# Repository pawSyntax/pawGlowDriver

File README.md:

# pawGlowDriver
Glow plug driver for multicyliner model ic engines. 
Can be used with 1-9 cylinders. Powered by 3 cell lipo. Interfaces with rc receiver for engine starting and variable onboard glow plug control. 
Arduino code to run on pro-mini. Eagle schematic and board files. CamBam file for pcb cutting.

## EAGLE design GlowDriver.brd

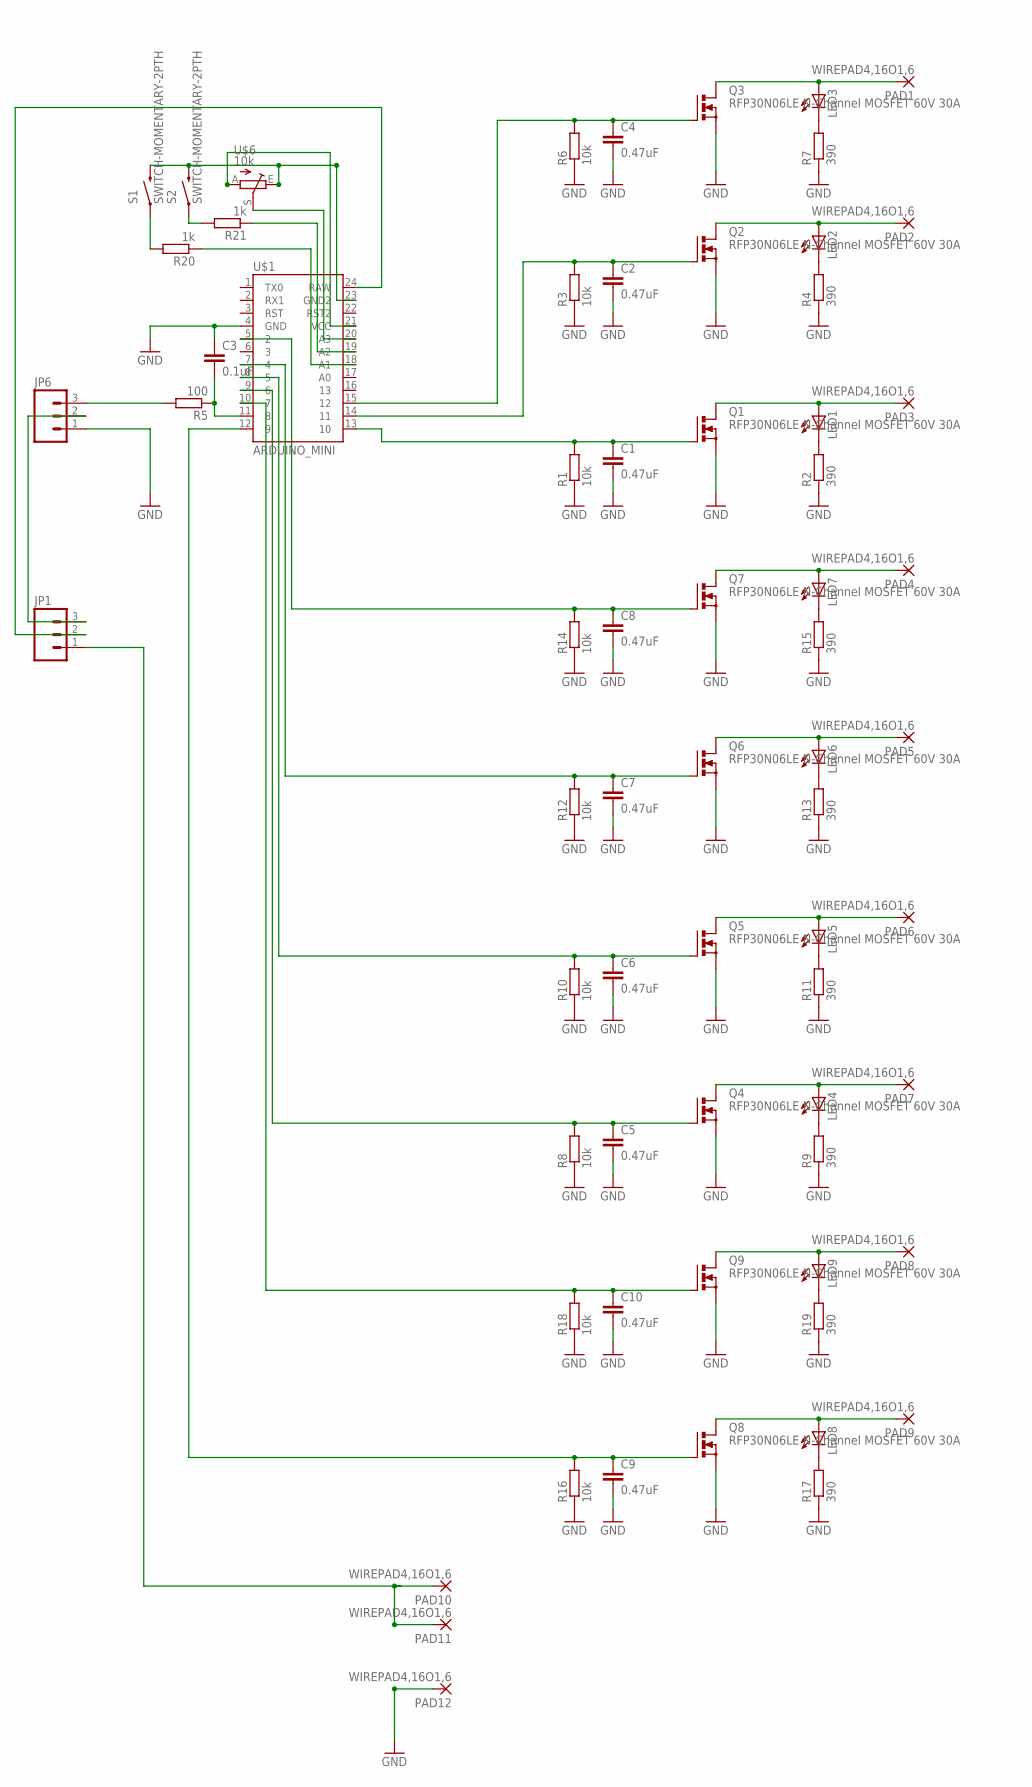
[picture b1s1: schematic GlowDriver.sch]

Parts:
C1, C2, C4, C5, C6, C7, C8, C9, C10: 0.47uF; CAP-PTH-SMALLEZ
C3: 0.1uF; C050-035X075
JP1, JP6: M03PTH; 1X03
LED1, LED2, LED3, LED4, LED5, LED6, LED7, LED8, LED9: LED5MM
PAD1, PAD2, PAD3, PAD4, PAD5, PAD6, PAD7, PAD8, PAD9, PAD10, PAD11, PAD12: WIREPAD4,16O1,6; 4,16O1,6
Q1, Q2, Q3, Q4, Q5, Q6, Q7, Q8, Q9: RFP30N06LE N-Channel MOSFET 60V 30A; TO220BV
R1, R3, R6, R8, R10, R12, R14, R16, R18: 10k; 0207/2V
R2, R4, R7, R9, R11, R13, R15, R17, R19: 390; 0207/2V
R5: 100; 0207/10
R20, R21: 1k; 0207/2V
S1, S2: SWITCH-MOMENTARY-2PTH; TACTILE-PTH
U$1: ARDUINO_MINI
U$6: 10k; PT-10

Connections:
GND: C1.2, C2.2, C3.1, C4.2, C5.2, C6.2, C7.2, C8.2, C9.2, C10.2, JP6.1, PAD12.1, Q1.S, Q2.S, Q3.S, Q4.S, Q5.S, Q6.S, Q7.S, Q8.S, Q9.S, R1.1, R2.1, R3.1, R4.1, R6.1, R7.1, R8.1, R9.1, R10.1, R11.1, R12.1, R13.1, R14.1, R15.1, R16.1, R17.1, R18.1, R19.1, U$1.4 (GND)
unnamed: LED1.K (C), R2.2
unnamed: C1.1, Q1.G, R1.2, U$1.13 (10)
unnamed: LED1.A, PAD3.1, Q1.D
unnamed: LED2.K (C), R4.2
unnamed: C2.1, Q2.G, R3.2, U$1.14 (11)
unnamed: LED2.A, PAD2.1, Q2.D
unnamed: LED4.K (C), R9.2
unnamed: JP1.2, U$1.24 (RAW)
unnamed: LED5.K (C), R11.2
unnamed: C6.1, Q5.G, R10.2, U$1.8 (5)
unnamed: C3.2, R5.1, U$1.11 (8)
unnamed: LED5.A, PAD6.1, Q5.D
unnamed: JP6.3, R5.2
unnamed: JP1.1, PAD10.1, PAD11.1
unnamed: U$1.20 (A3), U$6.S
unnamed: U$1.21 (VCC), U$6.A
unnamed: C10.1, Q9.G, R18.2, U$1.10 (7)
unnamed: C5.1, Q4.G, R8.2, U$1.9 (6)
unnamed: LED3.K (C), R7.2
unnamed: C4.1, Q3.G, R6.2, U$1.15 (12)
unnamed: LED3.A, PAD1.1, Q3.D
unnamed: LED4.A, PAD7.1, Q4.D
unnamed: JP1.3, JP6.2
unnamed: LED6.K (C), R13.2
unnamed: C7.1, Q6.G, R12.2, U$1.7 (4)
unnamed: LED6.A, PAD5.1, Q6.D
unnamed: LED7.K (C), R15.2
unnamed: C8.1, Q7.G, R14.2, U$1.5 (2)
unnamed: LED7.A, PAD4.1, Q7.D
unnamed: C9.1, Q8.G, R16.2, U$1.12 (9)
unnamed: LED8.K (C), R17.2
unnamed: LED8.A, PAD9.1, Q8.D
unnamed: LED9.K (C), R19.2
unnamed: R21.1, U$1.19 (A2)
unnamed: LED9.A, PAD8.1, Q9.D
unnamed: R20.1, U$1.18 (A1)
unnamed: R20.2, S1.1
unnamed: R21.2, S2.1
unnamed: S1.3 (2), S2.3 (2), U$1.23 (GND2), U$6.E

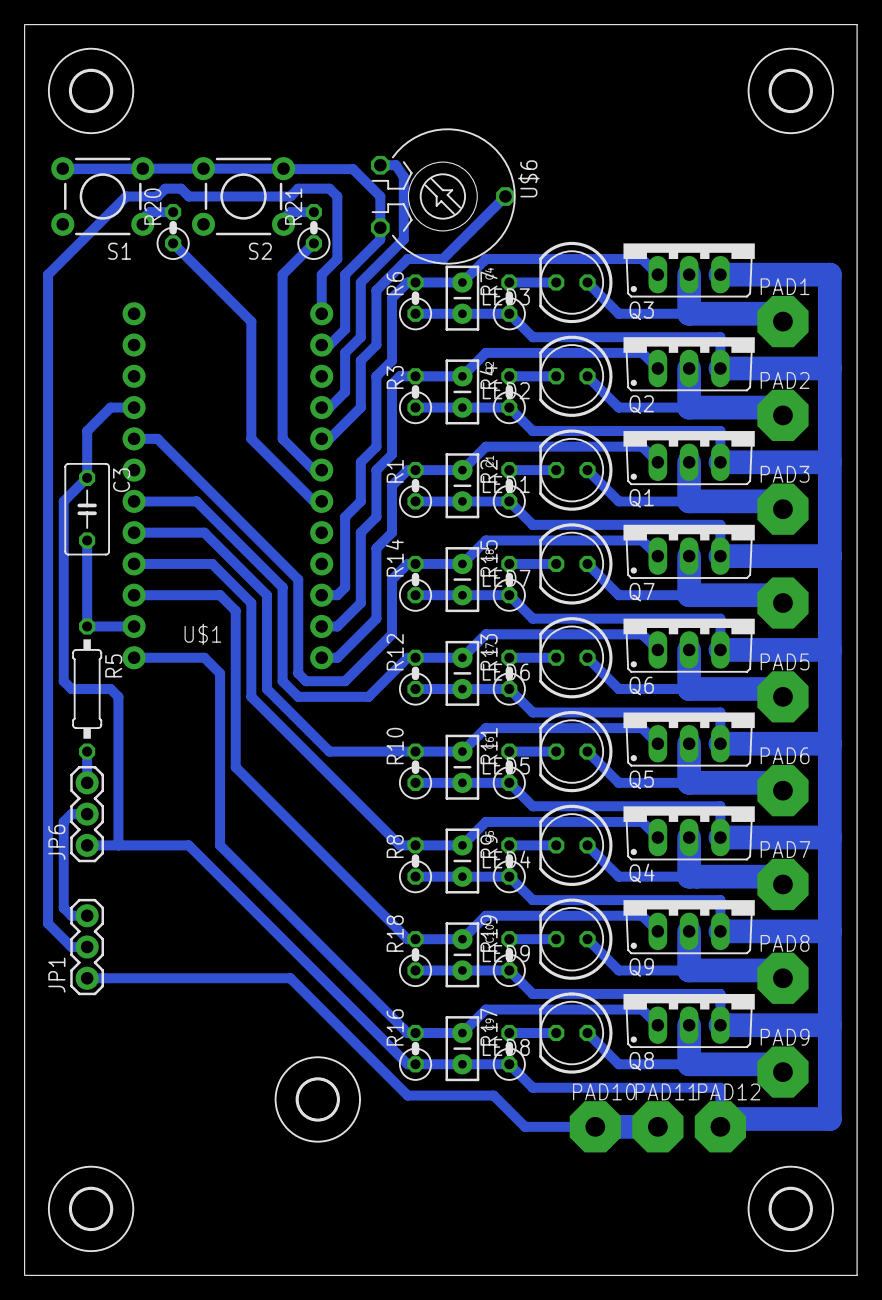
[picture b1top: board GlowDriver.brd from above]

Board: 2 copper layers, 67.6 x 101.6 mm, 72 parts (1 on the bottom side), 40 nets.

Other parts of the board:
U$2, U$3, U$4, U$5, U$8: 3,2

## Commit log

2019-06-03 Arduino code uploaded
2019-06-03 formatting changes
2019-06-03 update description
2019-06-03 trimmed end

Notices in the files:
parts and their libraries:
SparkFun-Connectors: Licensing: CC v3.0 Share-Alike You are welcome to use this library for commercial purposes.
